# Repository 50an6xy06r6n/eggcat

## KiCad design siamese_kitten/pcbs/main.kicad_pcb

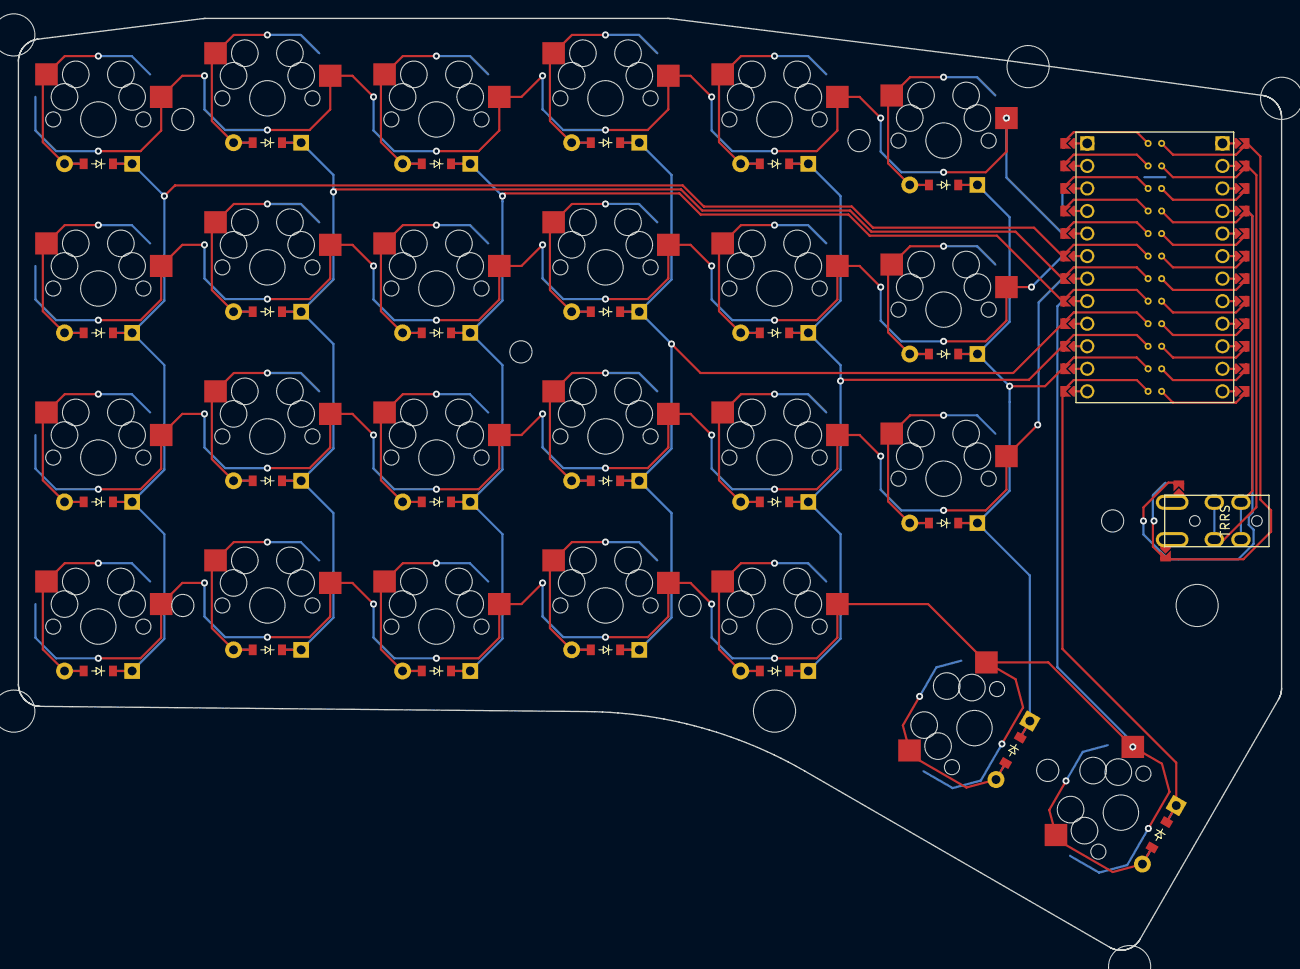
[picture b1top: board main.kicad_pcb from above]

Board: 2 copper layers, 142.3 x 105.0 mm, 59 parts (0 on the bottom side), 40 nets.

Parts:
D1, D3, D5, D7, D9, D11, D13, D15, D17, D19, D21, D23, D25, D27, D29, D31, D33, D35, D37, D39, D41, D43, D45, D47, D49: ComboDiode
MCU1: ProMicro_routed
Ref**: Val**; M2_standoff_hole
Ref**#2, Ref**#3, Ref**#4, Ref**#5, Ref**#6, Ref**#7: Val**; M2_standoff_hole
S1, S2, S3, S4, S5, S6, S7, S8, S9, S10, S11, S12, S13, S14, S15, S16, S17, S18, S19, S20, S21, S22, S23, S24, S25: MX
TRRS1: PJ-320A

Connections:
0_5|0|0|0_key1: D1.1, D1.2, S1.2
0_5|0|0|0_key2: D3.1, D3.2, S2.2
0_5|0|0|0_key3: D5.1, D5.2, S3.2
0_5|0|0|0_key4: D7.1, D7.2, S4.2
1_5|0|0|0_key5: D9.1, D9.2, S5.2
1_5|0|0|0_key6: D11.1, D11.2, S6.2
1_5|0|0|0_key7: D13.1, D13.2, S7.2
1_5|0|0|0_key8: D15.1, D15.2, S8.2
2_5|0|0|0_key9: D17.1, D17.2, S9.2
2_5|0|0|0_key10: D19.1, D19.2, S10.2
2_5|0|0|0_key11: D21.1, D21.2, S11.2
2_5|0|0|0_key12: D23.1, D23.2, S12.2
3_5|0|0|0_key13: D25.1, D25.2, S13.2
3_5|0|0|0_key14: D27.1, D27.2, S14.2
3_5|0|0|0_key15: D29.1, D29.2, S15.2
3_5|0|0|0_key16: D31.1, D31.2, S16.2
4_5|0|0|0_key17: D33.1, D33.2, S17.2
4_5|0|0|0_key18: D35.1, D35.2, S18.2
4_5|0|0|0_key19: D37.1, D37.2, S19.2
4_5|0|0|0_key20: D39.1, D39.2, S20.2
5_5|0|0|0_key21: D41.1, D41.2, S21.2
5_5|0|0|0_key22: D43.1, D43.2, S22.2
5_5|0|0|0_key23: D45.1, D45.2, S23.2
5_625|-60|4_875|4_625_key24: D47.1, D47.2, S24.2
5_625|-60|4_875|4_625_key25: D49.1, D49.2, S25.2
GND: MCU1.3, MCU1.4, MCU1.23, TRRS1.B
P0: MCU1.2, TRRS1.C
P1: MCU1.1, TRRS1.A
VCC: MCU1.21, TRRS1.D
col_0: D1.1, D1.2, D3.1, D3.2, D5.1, D5.2, D7.1, D7.2, MCU1.19
col_1: D9.1, D9.2, D11.1, D11.2, D13.1, D13.2, D15.1, D15.2, MCU1.18
col_2: D17.1, D17.2, D19.1, D19.2, D21.1, D21.2, D23.1, D23.2, MCU1.17
col_3: D25.1, D25.2, D27.1, D27.2, D29.1, D29.2, D31.1, D31.2, MCU1.16
col_4: D33.1, D33.2, D35.1, D35.2, D37.1, D37.2, D39.1, D39.2, MCU1.15
col_5: D41.1, D41.2, D43.1, D43.2, D45.1, D45.2, D49.1, D49.2, MCU1.14
col_6: D47.1, D47.2, MCU1.13
row_0: MCU1.5, S4.1, S8.1, S12.1, S16.1, S20.1, S23.1
row_1: MCU1.6, S3.1, S7.1, S11.1, S15.1, S19.1, S22.1
row_2: MCU1.7, S2.1, S6.1, S10.1, S14.1, S18.1, S21.1
row_3: MCU1.8, S1.1, S5.1, S9.1, S13.1, S17.1, S24.1, S25.1

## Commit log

2023-12-12 Initial port of existing data
